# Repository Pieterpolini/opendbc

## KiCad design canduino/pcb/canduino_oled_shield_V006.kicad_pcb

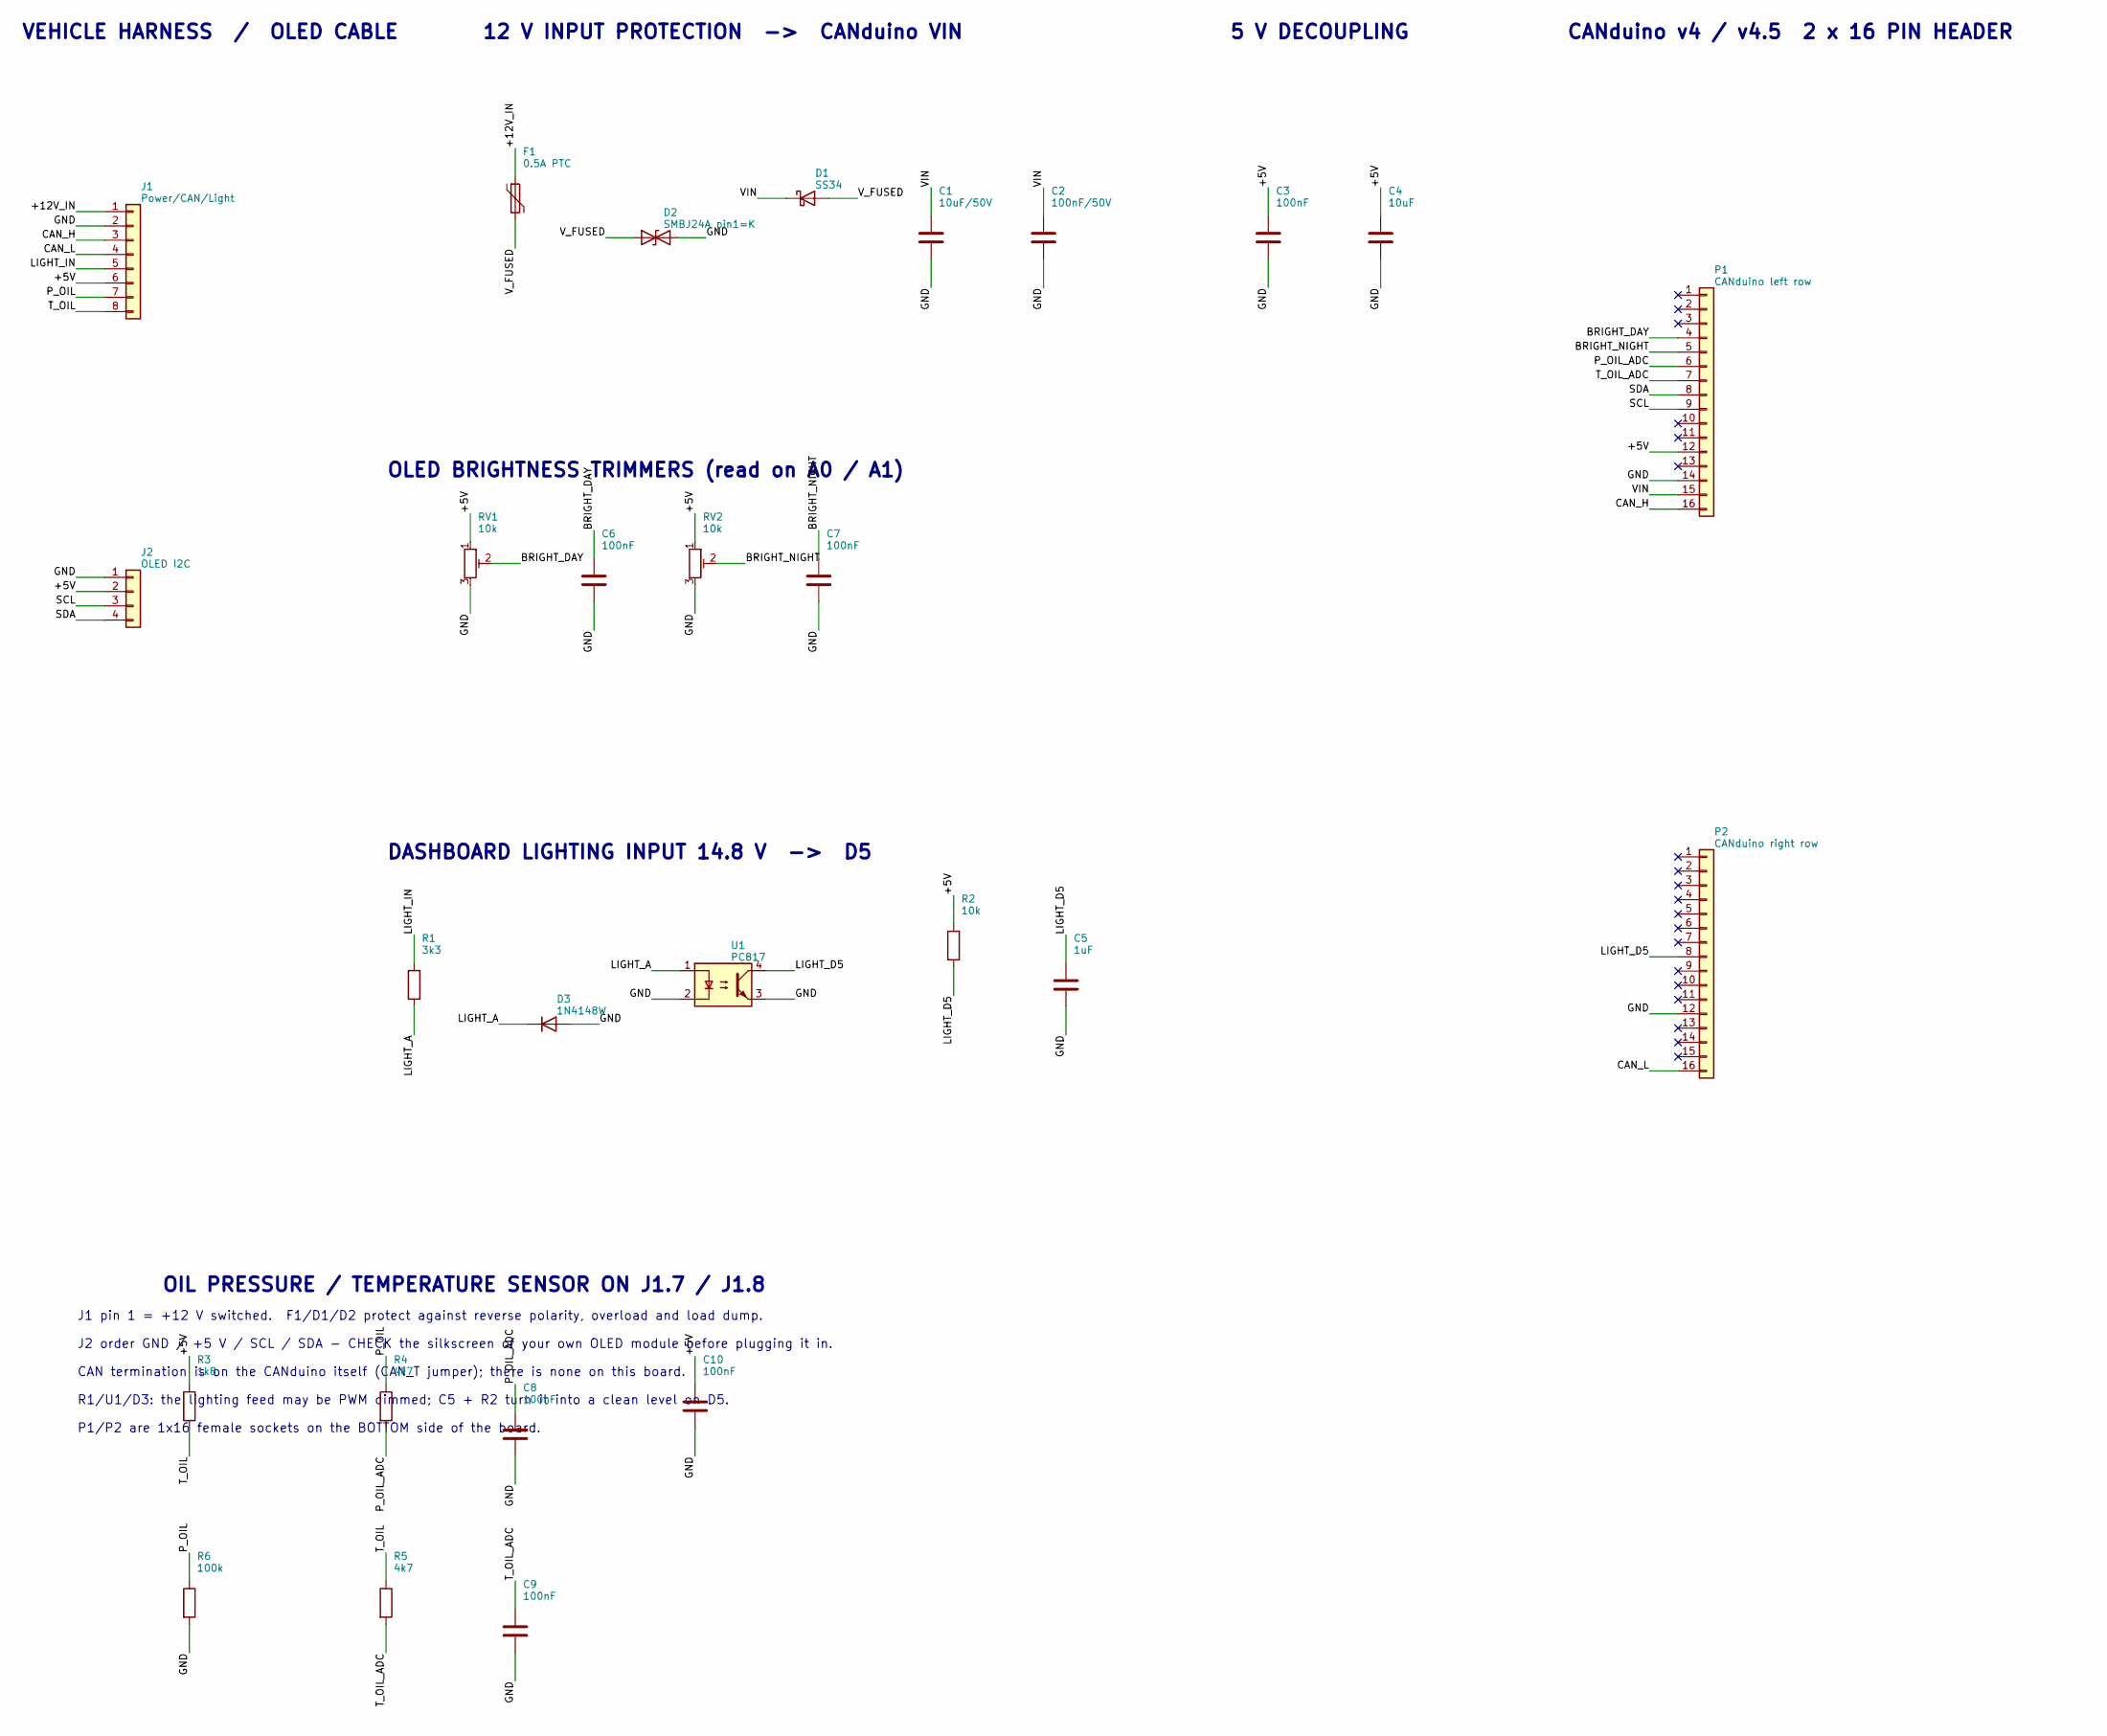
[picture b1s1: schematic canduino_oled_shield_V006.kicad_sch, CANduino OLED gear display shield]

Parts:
C1: 10uF/50V; C_1210_3225Metric
C2: 100nF/50V; C_0805_2012Metric
C3, C6, C7, C8, C9, C10: 100nF; C_0805_2012Metric
C4: 10uF; C_0805_2012Metric
C5: 1uF; C_0805_2012Metric
D1: SS34; D_SMA
D2: SMBJ24A pin1=K; D_SMB
D3: 1N4148W; D_SOD-123
F1: 0.5A PTC; Fuse_1206_3216Metric
J1: Power/CAN/Light; JST_XH_S8B-XH-A_1x08_P2.50mm_Horizontal
J2: OLED I2C; JST_XH_S4B-XH-A_1x04_P2.50mm_Horizontal
P1: CANduino left row; PinSocket_1x16_P2.54mm_Vertical
P2: CANduino right row; PinSocket_1x16_P2.54mm_Vertical
R1: 3k3; R_0805_2012Metric
R2: 10k; R_0805_2012Metric
R3: 1k8; R_0805_2012Metric
R4, R5: 4k7; R_0805_2012Metric
R6: 100k; R_0805_2012Metric
RV1, RV2: 10k; Potentiometer_Runtron_RM-065_Vertical
U1: PC817; DIP-4_W7.62mm

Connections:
+5V: C3.1, C4.1, C10.1, J1.6, J2.2, P1.12, R2.1, R3.1, RV1.1, RV2.1
+12V_IN: F1.1, J1.1
BRIGHT_DAY: C6.1, P1.4, RV1.2
BRIGHT_NIGHT: C7.1, P1.5, RV2.2
CAN_H: J1.3, P1.16
CAN_L: J1.4, P2.16
GND: C1.2, C2.2, C3.2, C4.2, C5.2, C6.2, C7.2, C8.2, C9.2, C10.2, D2.2 (A2), D3.2 (A), J1.2, J2.1, P1.14, P2.12, R6.2, RV1.3, RV2.3, U1.2, U1.3
LIGHT_A: D3.1 (K), R1.2, U1.1
LIGHT_D5: C5.1, P2.8, R2.2, U1.4
LIGHT_IN: J1.5, R1.1
P_OIL: J1.7, R4.1, R6.1
P_OIL_ADC: C8.1, P1.6, R4.2
SCL: J2.3, P1.9
SDA: J2.4, P1.8
T_OIL: J1.8, R3.2, R5.1
T_OIL_ADC: C9.1, P1.7, R5.2
VIN: C1.1, C2.1, D1.1 (K), P1.15
V_FUSED: D1.2 (A), D2.1 (A1), F1.2

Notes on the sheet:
VEHICLE HARNESS / OLED CABLE
12 V INPUT PROTECTION -> CANduino VIN
5 V DECOUPLING
OLED BRIGHTNESS TRIMMERS (read on A0 / A1)
DASHBOARD LIGHTING INPUT 14.8 V -> D5
OIL PRESSURE / TEMPERATURE SENSOR ON J1.7 / J1.8
CANduino v4 / v4.5 2 x 16 PIN HEADER
J1 pin 1 = +12 V switched. F1/D1/D2 protect against reverse polarity, overload and load dump.
J2 order GND / +5 V / SCL / SDA - CHECK the silkscreen of your own OLED module before plugging it in.
CAN termination is on the CANduino itself (CAN_T jumper); there is none on this board.
R1/U1/D3: the lighting feed may be PWM dimmed; C5 + R2 turn it into a clean level on D5.
P1/P2 are 1x16 female sockets on the BOTTOM side of the board.

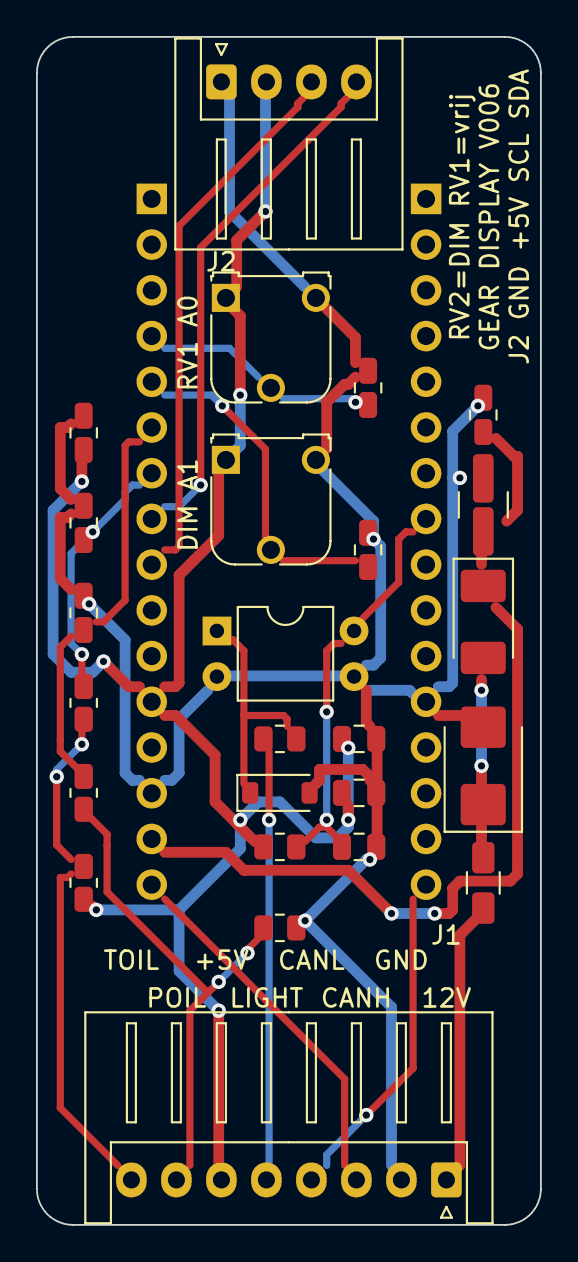
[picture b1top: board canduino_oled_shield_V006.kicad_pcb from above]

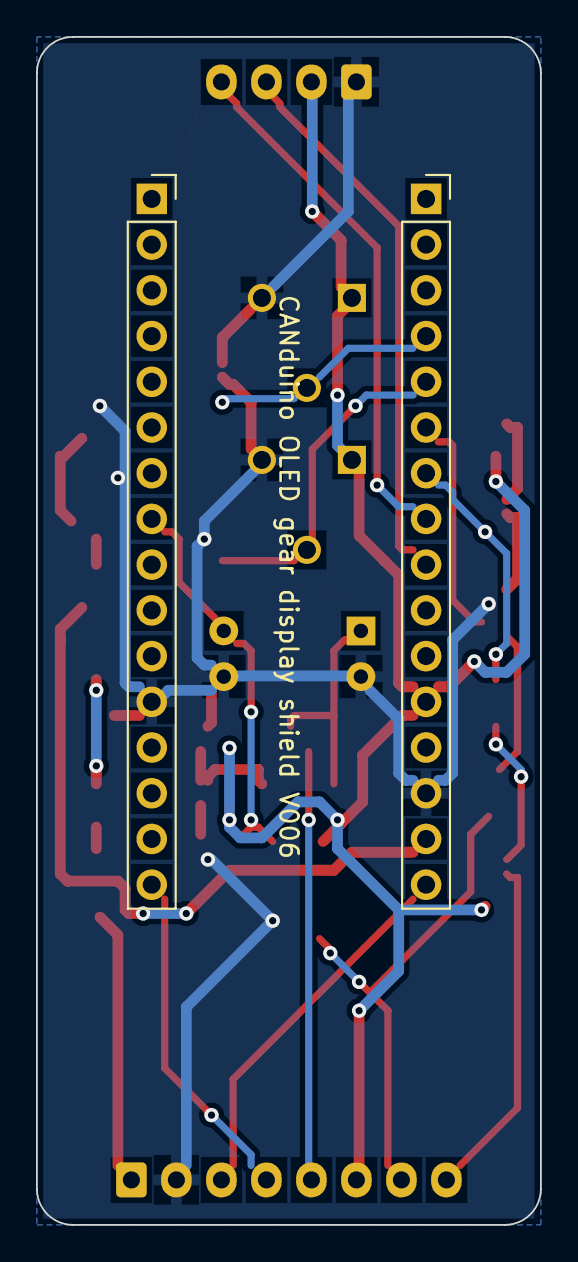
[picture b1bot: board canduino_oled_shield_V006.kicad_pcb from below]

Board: 2 copper layers, 28.0 x 66.0 mm, 27 parts (2 on the bottom side), 18 nets.

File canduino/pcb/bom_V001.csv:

Ref,Value,Footprint,Side,Function,Suggested part
J1,Power/CAN/Light,JST_XH_S8B-XH-A_1x08_P2.50mm_Horizontal,F,"JST S8B-XH-A, right angle, 2.50 mm",JST S8B-XH-A
J2,OLED I2C,PinHeader_1x04_P2.54mm_Horizontal,F,"1x4 male, right angle, 2.54 mm",2.54mm 1x4 male right angle
P1,CANduino left row,PinSocket_1x16_P2.54mm_Vertical,B,"1x16 female socket, bottom side",generic
P2,CANduino right row,PinSocket_1x16_P2.54mm_Vertical,B,"1x16 female socket, bottom side",generic
F1,0.5A PTC,Fuse_1206_3216Metric,F,"PTC resettable fuse, 1206, Ihold 0.5 A, 60 V",Littelfuse 1206L050YR
D1,SS34,D_SMA,F,"Schottky 40 V / 3 A, SMA, reverse-polarity series diode",SS34 / SK34A
D2,SMBJ24A pin1=K,D_SMB,F,"Unidirectional TVS 24 V, SMB, pin 1 = cathode (band)",SMBJ24A
D3,1N4148W,D_SOD-123,F,"Reverse protection across the opto LED, SOD-123",1N4148W
U1,PC817,DIP-4_W7.62mm,F,"Opto-coupler, DIP-4",PC817 / EL817 / LTV-817
RV1,10k,Potentiometer_Runtron_RM-065_Vertical,F,"Trimmer RM-065 / 3362P, level 1 = day",Bourns 3362P-1-103LF or RM-065 10k
RV2,10k,Potentiometer_Runtron_RM-065_Vertical,F,"Trimmer RM-065 / 3362P, level 2 = night",Bourns 3362P-1-103LF or RM-065 10k
R1,3k3,R_0805_2012Metric,F,"LED series resistor, 0805, >=1/8 W",any 0805 1%
R2,10k,R_0805_2012Metric,F,"Pull-up for D5, 0805",any 0805 1%
C1,10uF/50V,C_1210_3225Metric,F,X7R 1210,X7R 50 V
C2,100nF/50V,C_0805_2012Metric,F,X7R 0805,X7R 50 V
C3,100nF,C_0805_2012Metric,F,X7R 0805,X7R 50 V
C4,10uF,C_0805_2012Metric,F,X5R 0805,X5R/X7R 16 V
C5,1uF,C_0805_2012Metric,F,"Filters PWM dimming on the lighting feed, 0805",X7R 16 V
